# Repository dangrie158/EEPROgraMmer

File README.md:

# EEPROgraMmer

**Arduino EEPROM Programmer**

Universal Programmer for parallel EEPROMS using a python CLI and a simple Arduino with 2 shift-registers to interface the EEPROM.

Based on the [Arduino Code](https://github.com/beneater/eeprom-programmer) written by [Ben Eater](https://eater.net).

## Schematic

check out the [original project](https://github.com/beneater/eeprom-programmer)

## Synopsys

```
usage: eepro [-h] -p PORT [-f FILE] [-b BAUD] [-s SIZE] [-w | -r] [-v] [-c]
             [--check-empty]

Write to or read from an EEPROM

optional arguments:
  -h, --help            show this help message and exit
  -p PORT, --port PORT  serial port to the programmer
  -f FILE, --file FILE  binary file to write
  -b BAUD, --baud BAUD  baudrate for communication with the programmer
  -s SIZE, --size SIZE  size of the EEPROM in bytes
  -w                    write <file> to the EEPROM
  -r                    read the contents of the EEPROM into file
  -v                    verify file contents after writing
  -c                    clear the EEPROM (with 0xff bytes) before writing or
                        reading
  --check-empty         make sure the EEPROM is empty (filled with 0xff)
```

## Examples

### Clear an EEPROM

Clear the first 2048 bytes of the EEPROM and read back to make sure they are set accordingly

```
./eepro --port /dev/tty.wchusbserial1440 -c --check-empty -s=2048
```

### Write a binary file to the EEPROM

The following command will clear the EEPROM, write the contents of ```firmware.bin``` and reads back the content

```
./eepro --port /dev/tty.wchusbserial1440 -cvwf firmware.bin -s=2048
``` 

### Dump EEPROM Contents

Read the first 2048 bytes of the EEPROM and write the result into ```firmware.bin```. The content is then read again to check against errors.

```
./eepro --port /dev/tty.wchusbserial1440 -vrf firmware.bin -s=2048
```

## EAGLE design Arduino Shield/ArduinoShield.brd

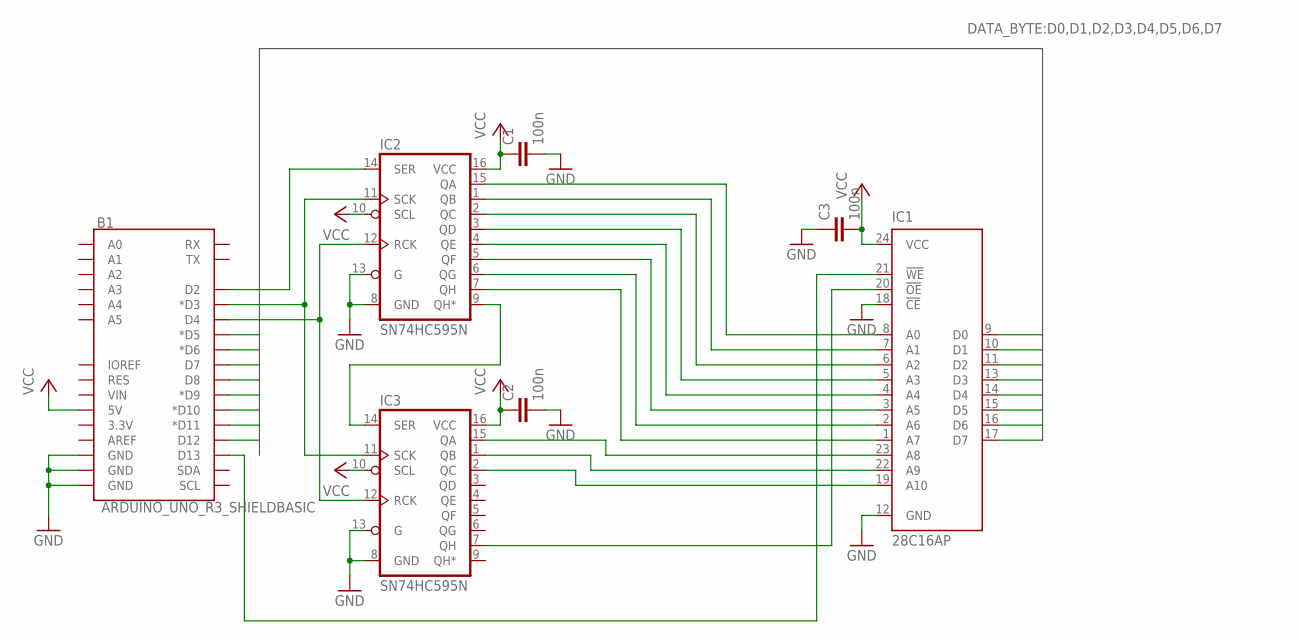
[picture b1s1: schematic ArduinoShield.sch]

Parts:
B1: ARDUINO_UNO_R3_SHIELDBASIC; UNO_R3_SHIELD
C1, C2, C3: 100n; C050-024X044
IC1: 28C16AP; DIL24-6
IC2, IC3: SN74HC595N; DIP16

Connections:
D0: B1.D5 (*D5), IC1.9 (D0)
D1: B1.D6 (*D6), IC1.10 (D1)
D2: B1.D7, IC1.11 (D2)
D3: B1.D8, IC1.13 (D3)
D4: B1.D9 (*D9), IC1.14 (D4)
D5: B1.D10 (*D10), IC1.15 (D5)
D6: B1.D11 (*D11), IC1.16 (D6)
D7: B1.D12, IC1.17 (D7)
GND: B1.GND@0 (GND), B1.GND@1 (GND), B1.GND@2 (GND), C1.2, C2.2, C3.1, IC1.12 (GND), IC1.18 (!CE), IC2.8 (GND), IC2.13 (G), IC3.8 (GND), IC3.13 (G)
unnamed: B1.D2, IC2.14 (SER)
unnamed: IC2.9 (QH*), IC3.14 (SER)
unnamed: B1.D3 (*D3), IC2.11 (SCK), IC3.11 (SCK)
unnamed: B1.D13, IC1.21 (!WE)
unnamed: B1.D4, IC2.12 (RCK), IC3.12 (RCK)
unnamed: IC1.8 (A0), IC2.15 (QA)
unnamed: IC1.7 (A1), IC2.1 (QB)
unnamed: IC1.6 (A2), IC2.2 (QC)
unnamed: IC1.5 (A3), IC2.3 (QD)
unnamed: IC1.4 (A4), IC2.4 (QE)
unnamed: IC1.3 (A5), IC2.5 (QF)
unnamed: IC1.2 (A6), IC2.6 (QG)
unnamed: IC1.1 (A7), IC2.7 (QH)
unnamed: IC1.23 (A8), IC3.15 (QA)
unnamed: IC1.22 (A9), IC3.1 (QB)
unnamed: IC1.19 (A10), IC3.2 (QC)
unnamed: IC1.20 (!OE), IC3.7 (QH)
VCC: B1.5V, C1.1, C2.1, C3.2, IC1.24 (VCC), IC2.10 (SCL), IC2.16 (VCC), IC3.10 (SCL), IC3.16 (VCC)

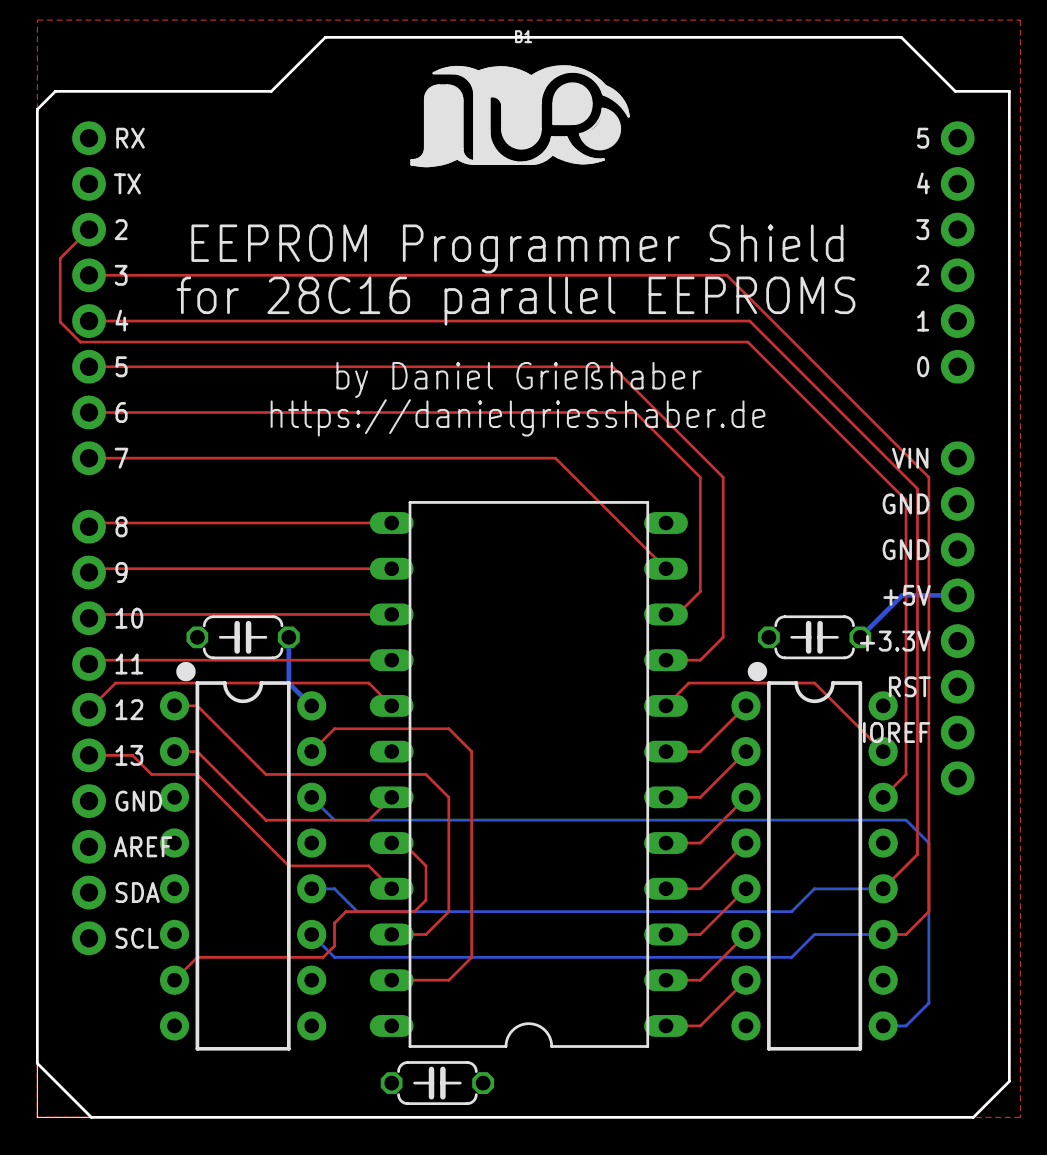
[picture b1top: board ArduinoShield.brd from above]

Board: 2 copper layers, 54.0 x 60.0 mm, 8 parts (0 on the bottom side), 27 nets.

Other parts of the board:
U$1: LOGO-SILKSCREEN

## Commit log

2019-08-03 added README
2019-08-03 added synopsys to README
2019-08-03 removed .vscode directory
2019-08-04 added read functionality
2019-08-04 added examples to README
2019-08-04 added docstrings to most methods
2019-08-04 added tyoe annotations and formatting
2019-08-04 configures setuptools
2019-08-04 moved to ReST format for README
2019-08-04 restructured Project for distribution
2019-08-04 added section about installation to README
2019-08-04 added check for fileparameter when verifying
2019-08-04 bumped version to 0.2.0
2019-08-05 added arduino shield form factor board for ZIF-Socket and Shift registers
2019-08-25 added banner image of assembled shield
2019-08-25 fixed links to proper rest syntax
2020-02-29 explicitly specified data type length in arduino code to fix an overflow issue

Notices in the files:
parts and their libraries:
SparkFun-Boards: Licensing: Creative Commons ShareAlike 4.0 International - https://creativecommons.org/licenses/by-sa/4.0
